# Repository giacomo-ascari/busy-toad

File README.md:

# busy-toad

## Intro

Stereophonic sound fx processor with line/instrument support, plus dedicated stereo headphone output.

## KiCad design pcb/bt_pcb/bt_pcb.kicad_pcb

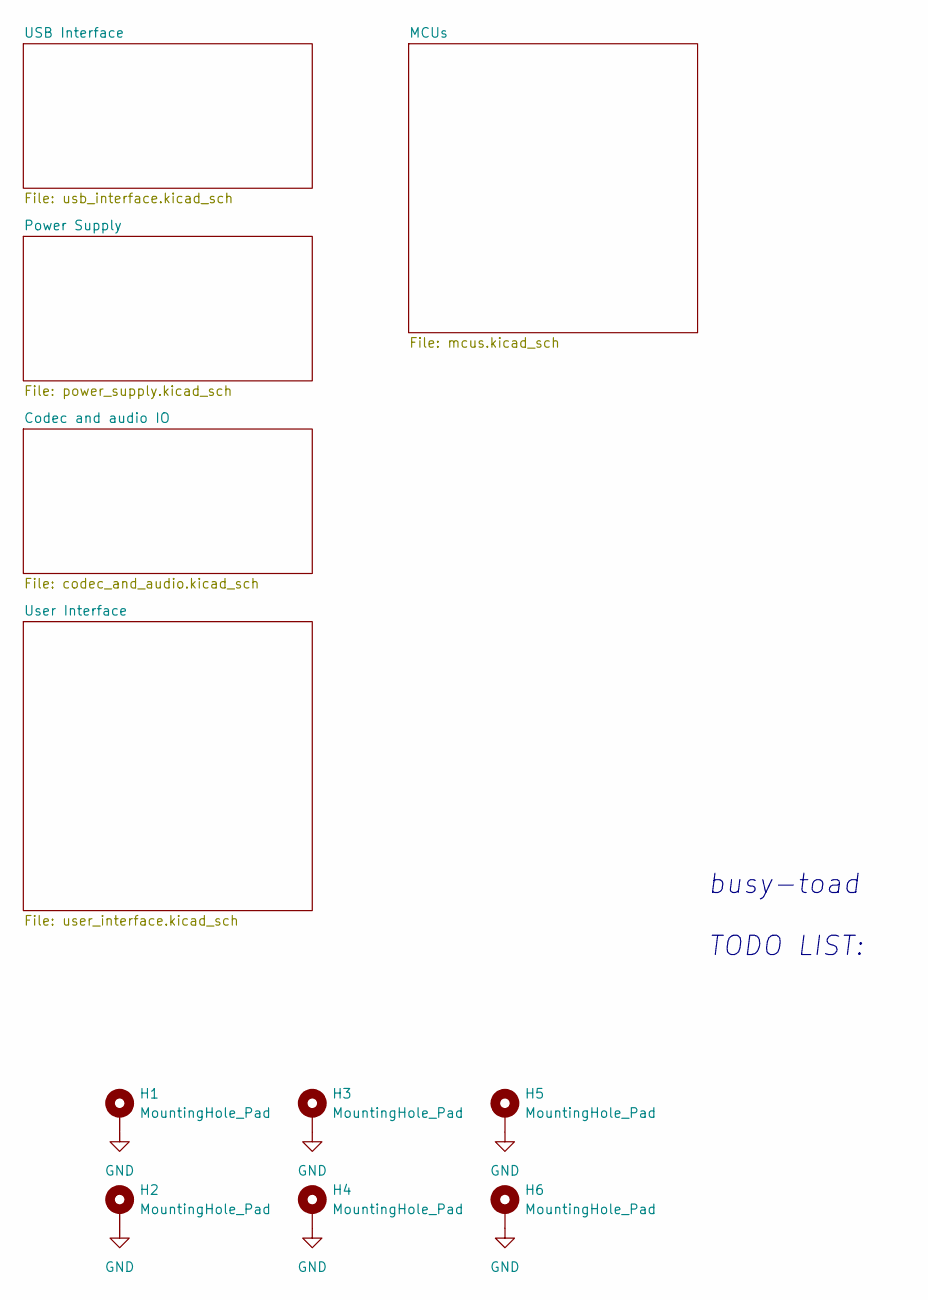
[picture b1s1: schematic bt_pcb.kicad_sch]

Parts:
H1, H2, H3, H4, H5, H6: MountingHole_Pad; MountingHole_3.2mm_M3_ISO14580_Pad

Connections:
GND: H1.1 (1_1), H2.1 (1_1), H3.1 (1_1), H4.1 (1_1), H5.1 (1_1), H6.1 (1_1); also elsewhere on the board

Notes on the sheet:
busy-toad TODO LIST:

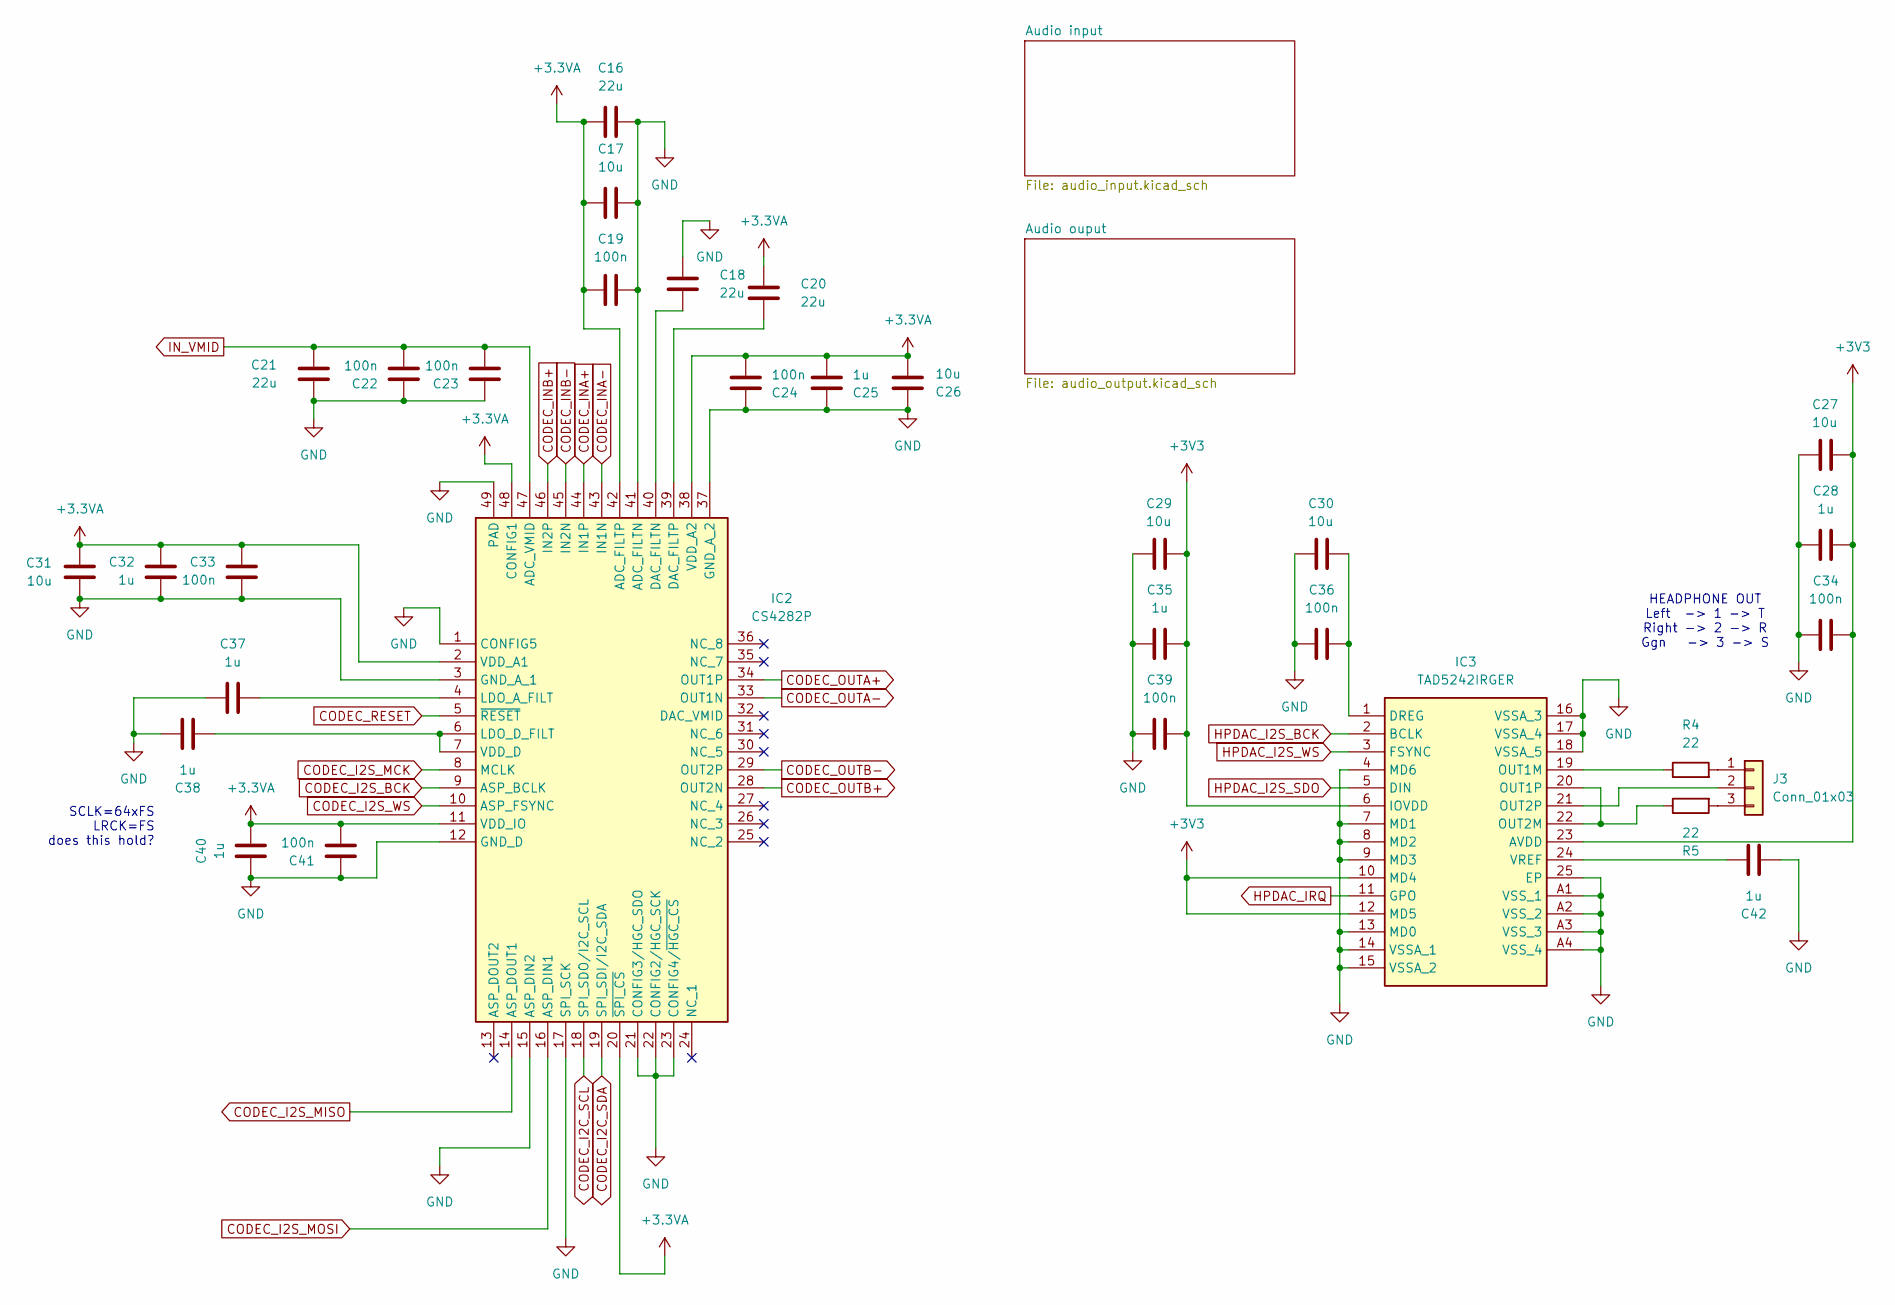
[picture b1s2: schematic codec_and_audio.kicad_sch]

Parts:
C16, C18, C20, C21: 22u; C_0805_2012Metric_Pad1.18x1.45mm_HandSolder
C17, C26, C27, C29, C30, C31: 10u; C_0805_2012Metric_Pad1.18x1.45mm_HandSolder
C19, C22, C23, C24, C33, C34, C36, C39, C41: 100n; C_0603_1608Metric_Pad1.08x0.95mm_HandSolder
C25, C28, C32, C35, C37, C38, C40, C42: 1u; C_0603_1608Metric_Pad1.08x0.95mm_HandSolder
IC2: CS4282P; QFN40P600X600X80-49N-D; Manufacturer_Part_Number CS4282P
IC3: TAD5242IRGER; Manufacturer_Part_Number TAD5242IRGER; Mouser Part Number 595-TAD5242IRGER
J3: Conn_01x03; JST_PH_B3B-PH-K_1x03_P2.00mm_Vertical
R4, R5: 22; R_0603_1608Metric_Pad0.98x0.95mm_HandSolder

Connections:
+3.3VA: C16.1, C17.2, C19.2, C20.1, C24.2, C25.2, C26.2, C31.1, C32.1, C33.1, C40.1, C41.2, IC2.2 (VDD_A1), IC2.11 (VDD_IO), IC2.20 (~SPI_CS), IC2.38 (VDD_A2), IC2.42 (ADC_FILTP), IC2.48 (CONFIG1); also elsewhere on the board
+3V3: C27.1, C28.1, C29.1, C34.2, C35.1, C39.2, IC3.6 (IOVDD), IC3.10 (MD4), IC3.12 (MD5), IC3.23 (AVDD); also elsewhere on the board
CODEC_I2C_SCL: IC2.18 (SPI_SDO/I2C_SCL); also elsewhere on the board
CODEC_I2C_SDA: IC2.19 (SPI_SDI/I2C_SDA); also elsewhere on the board
CODEC_I2S_BCK: IC2.9 (ASP_BCLK); also elsewhere on the board
CODEC_I2S_MCK: IC2.8 (MCLK); also elsewhere on the board
CODEC_I2S_MISO: IC2.14 (ASP_DOUT1); also elsewhere on the board
CODEC_I2S_MOSI: IC2.16 (ASP_DIN1); also elsewhere on the board
CODEC_I2S_WS: IC2.10 (ASP_FSYNC); also elsewhere on the board
CODEC_INA+: IC2.44 (IN1P); also elsewhere on the board
CODEC_INA-: IC2.43 (IN1N); also elsewhere on the board
CODEC_INB+: IC2.46 (IN2P); also elsewhere on the board
CODEC_INB-: IC2.45 (IN2N); also elsewhere on the board
CODEC_OUTA+: IC2.34 (OUT1P); also elsewhere on the board
CODEC_OUTA-: IC2.33 (OUT1N); also elsewhere on the board
CODEC_OUTB+: IC2.28 (OUT2N); also elsewhere on the board
CODEC_OUTB-: IC2.29 (OUT2P); also elsewhere on the board
CODEC_RESET: IC2.5 (~RESET); also elsewhere on the board
GND: C16.2, C17.1, C18.1, C19.1, C21.2, C22.1, C23.1, C24.1, C25.1, C26.1, C27.2, C28.2, C29.2, C30.2, C31.2, C32.2, C33.2, C34.1, C35.2, C36.1, C37.2, C38.2, C39.1, C40.2, C41.1, C42.2, IC2.1 (CONFIG5), IC2.3 (GND_A_1), IC2.12 (GND_D), IC2.15 (ASP_DIN2), IC2.17 (SPI_SCK), IC2.21 (CONFIG3/HGC_SDO), IC2.22 (CONFIG2/HGC_SCK), IC2.23 (CONFIG4/~HGC_CS), IC2.37 (GND_A_2), IC2.41 (ADC_FILTN), IC2.49 (PAD), IC3.4 (MD6), IC3.7 (MD1), IC3.8 (MD2), IC3.9 (MD3), IC3.13 (MD0), IC3.14 (VSSA_1), IC3.15 (VSSA_2), IC3.16 (VSSA_3), IC3.17 (VSSA_4), IC3.18 (VSSA_5), IC3.25 (EP), IC3.A1 (VSS_1), IC3.A2 (VSS_2), IC3.A3 (VSS_3), IC3.A4 (VSS_4); also elsewhere on the board
HPDAC_I2S_BCK: IC3.2 (BCLK); also elsewhere on the board
HPDAC_I2S_SDO: IC3.5 (DIN); also elsewhere on the board
HPDAC_I2S_WS: IC3.3 (FSYNC); also elsewhere on the board
HPDAC_IRQ: IC3.11 (GPO); also elsewhere on the board
IN_VMID: C21.1, C22.2, C23.2, IC2.47 (ADC_VMID); also elsewhere on the board
unnamed: C18.2, IC2.40 (DAC_FILTN)
unnamed: C20.2, IC2.39 (DAC_FILTP)
unnamed: C37.1, IC2.4 (LDO_A_FILT)
unnamed: C38.1, IC2.6 (LDO_D_FILT), IC2.7 (VDD_D)
unnamed: C30.1, C36.2, IC3.1 (DREG)
unnamed: IC3.19 (OUT1M), R4.1
unnamed: IC3.20 (OUT1P), IC3.22 (OUT2M), R5.1
unnamed: IC3.21 (OUT2P), J3.2
unnamed: C42.1, IC3.24 (VREF)
unnamed: J3.1, R4.2
unnamed: J3.3, R5.2

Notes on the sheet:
HEADPHONE OUT Left -> 1 -> T Right -> 2 -> R Ggn -> 3 -> S
SCLK=64xFS LRCK=FS does this hold?

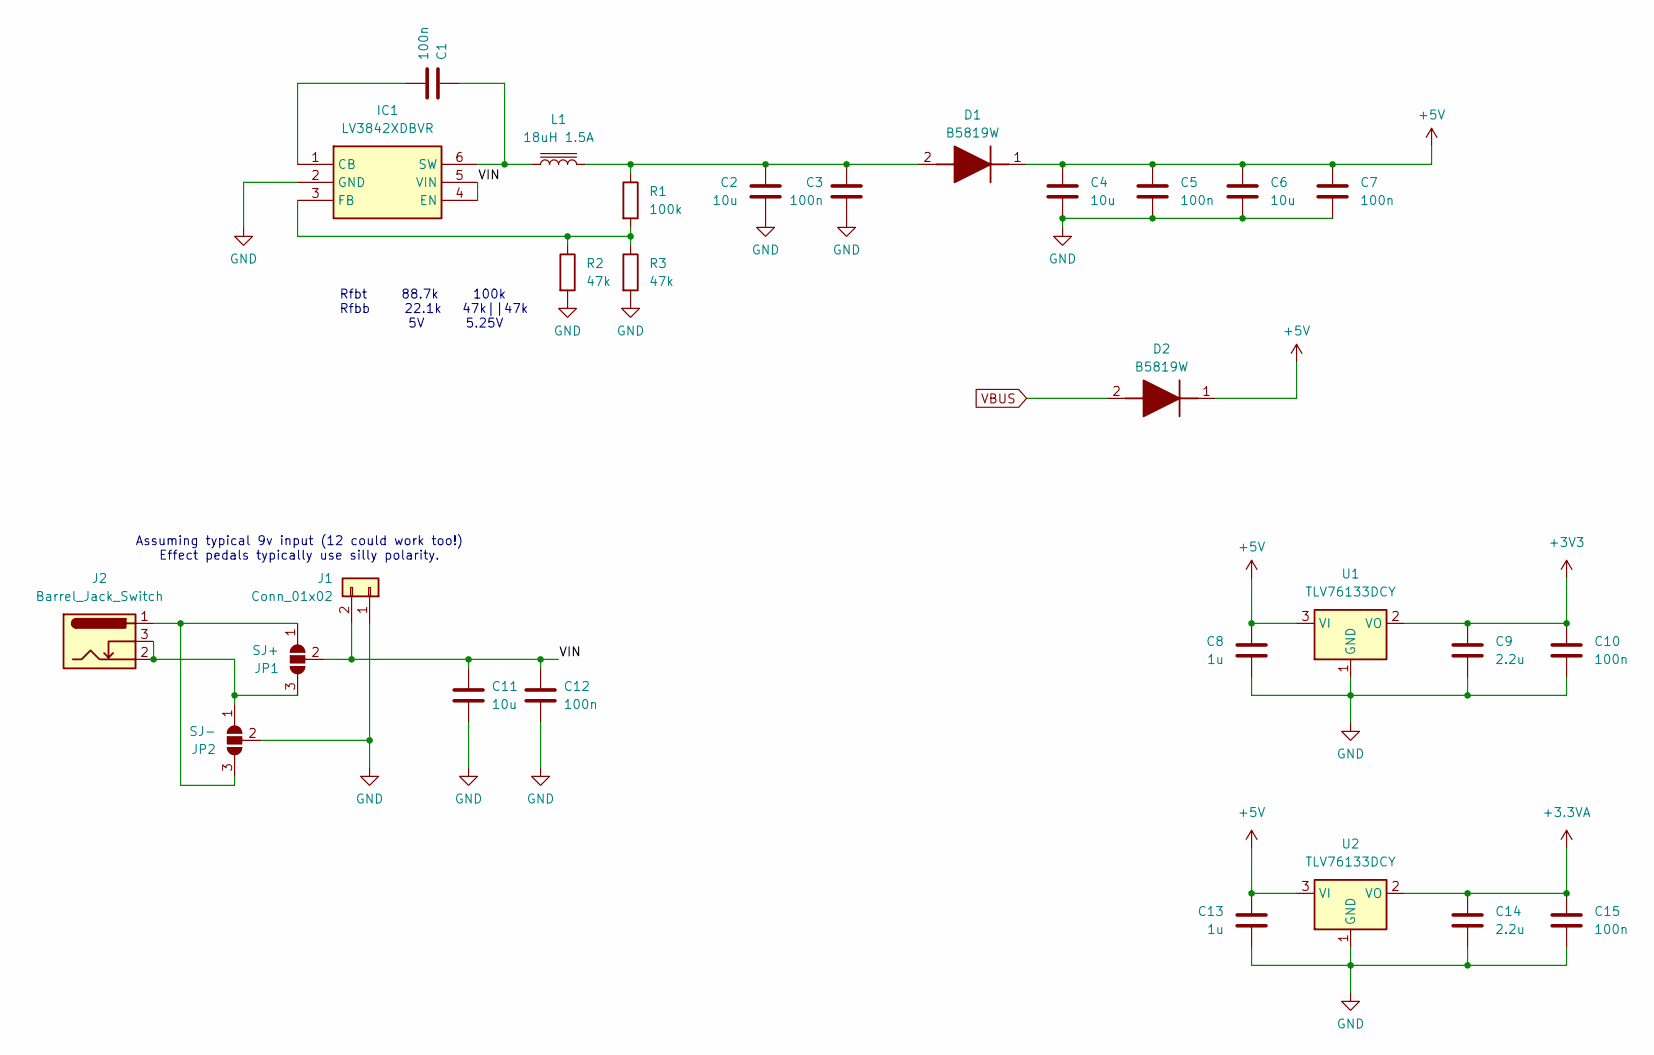
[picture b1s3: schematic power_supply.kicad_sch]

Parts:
C1, C3, C5, C7, C10, C12, C15: 100n; C_0603_1608Metric_Pad1.08x0.95mm_HandSolder
C2, C4, C6, C11: 10u; C_0805_2012Metric_Pad1.18x1.45mm_HandSolder
C8, C13: 1u; C_0603_1608Metric_Pad1.08x0.95mm_HandSolder
C9, C14: 2.2u; C_0603_1608Metric_Pad1.08x0.95mm_HandSolder
D1, D2: B5819W; SOD3716X125N; Manufacturer_Part_Number B5819W
IC1: LV3842XDBVR; SOT95P280X145-6N; Manufacturer_Part_Number LV3842XDBVR; Mouser Part Number 595-LV3842XDBVR
J1: Conn_01x02; PinHeader_1x02_P2.54mm_Vertical
J2: Barrel_Jack_Switch; 694106301002_1
JP1: SJ+; SolderJumper-3_P1.3mm_Open_Pad1.0x1.5mm
JP2: SJ-; SolderJumper-3_P1.3mm_Open_Pad1.0x1.5mm
L1: 18uH 1.5A; SRR6040A180M
R1: 100k; R_0603_1608Metric_Pad0.98x0.95mm_HandSolder
R2, R3: 47k; R_0603_1608Metric_Pad0.98x0.95mm_HandSolder
U1, U2: TLV76133DCY; SOT-223-3_TabPin2

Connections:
+3.3VA: C14.2, C15.1, U2.2 (VO); also elsewhere on the board
+3V3: C9.2, C10.1, U1.2 (VO); also elsewhere on the board
+5V: C4.1, C5.1, C6.1, C7.1, C8.2, C13.2, D1.1 (K), D2.1 (K), U1.3 (VI), U2.3 (VI)
/Power Supply/VIN: C11.1, C12.1, IC1.4 (EN), IC1.5 (VIN), J1.2, JP1.2 (C)
GND: C2.2, C3.2, C4.2, C5.2, C6.2, C7.2, C8.1, C9.1, C10.2, C11.2, C12.2, C13.1, C14.1, C15.2, IC1.2 (GND), J1.1, JP2.2 (C), R2.2, R3.2, U1.1 (GND), U2.1 (GND); also elsewhere on the board
unnamed: C2.1, C3.1, D1.2 (A), L1.2, R1.1
unnamed: C1.2, IC1.1 (CB)
unnamed: IC1.3 (FB), R1.2, R2.1, R3.1
unnamed: C1.1, IC1.6 (SW), L1.1
unnamed: J2.1, JP1.1 (A), JP2.3 (B)
unnamed: J2.2, J2.3, JP1.3 (B), JP2.1 (A)
VBUS: D2.2 (A); also elsewhere on the board

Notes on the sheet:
Assuming typical 9v input (12 could work too!) Effect pedals typically use silly polarity.
Rfbt 88.7k 100k Rfbb 22.1k 47k||47k 5V 5.25V

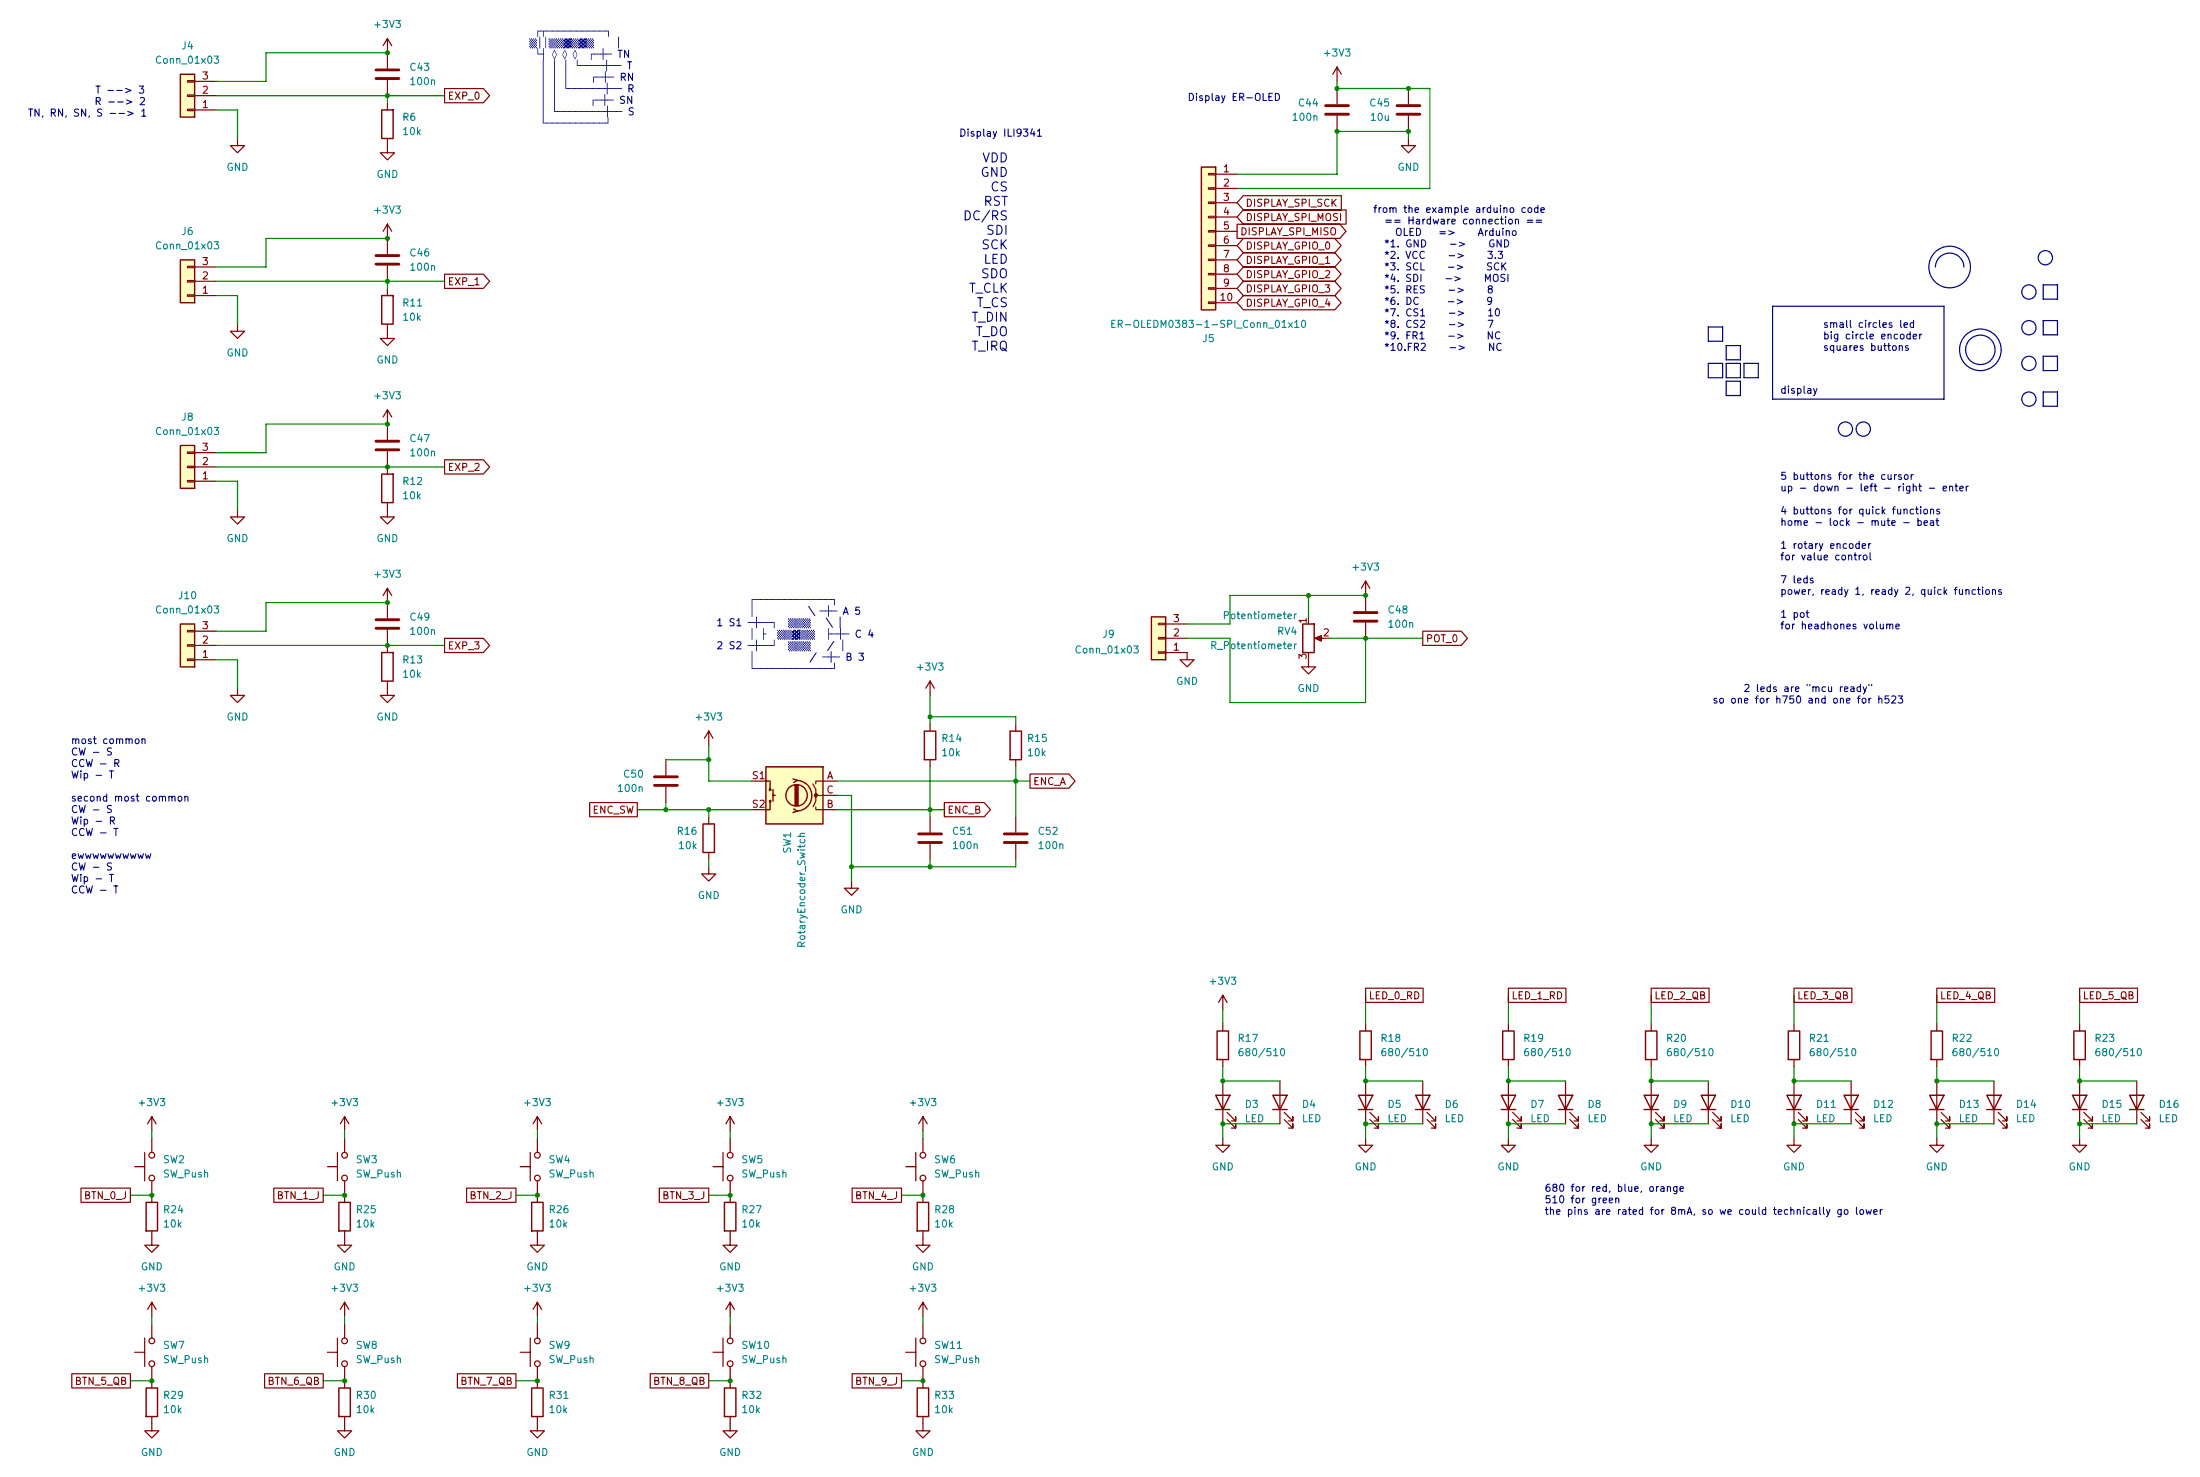
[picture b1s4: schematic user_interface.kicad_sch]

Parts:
C43, C44, C46, C47, C48, C49, C50, C51, C52: 100n; C_0603_1608Metric_Pad1.08x0.95mm_HandSolder
C45: 10u; C_0805_2012Metric_Pad1.18x1.45mm_HandSolder
D3, D5, D7, D9, D11, D13, D15: LED; LED_0603_1608Metric_Pad1.05x0.95mm_HandSolder
D4, D6, D8, D10, D12, D14, D16: LED; LED_D3.0mm
J4, J6, J8, J9, J10: Conn_01x03; JST_PH_B3B-PH-K_1x03_P2.00mm_Vertical
J5: ER-OLEDM0383-1-SPI_Conn_01x10; ER-OLEDM0383-1-SPI
R6, R11, R12, R13, R14, R15, R16, R24, R25, R26, R27, R28, R29, R30, R31, R32, R33: 10k; R_0603_1608Metric_Pad0.98x0.95mm_HandSolder
R17, R18, R19, R20, R21, R22, R23: 680/510; R_0603_1608Metric_Pad0.98x0.95mm_HandSolder
RV4: R_Potentiometer; Potentiometer_Alpha_RD901F-40-00D_Single_Vertical_CircularH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
SW1: RotaryEncoder_Switch; RotaryEncoder_Alps_EC11E-Switch_Vertical_H20mm_CircularMoun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
SW2, SW3, SW4, SW5, SW6, SW7, SW8, SW9, SW10, SW11: SW_Push; SW_TH_Tactile_Omron_B3F-102x

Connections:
+3V3: C43.1, C44.2, C45.2, C46.1, C47.1, C48.1, C49.1, C50.1, J4.3, J5.2, J6.3, J8.3, J9.3, J10.3, R14.1, R15.1, R17.1, RV4.1, SW1.S1, SW2.2, SW3.2, SW4.2, SW5.2, SW6.2, SW7.2, SW8.2, SW9.2, SW10.2, SW11.2; also elsewhere on the board
BTN_0_J: R24.1, SW2.1; also elsewhere on the board
BTN_1_J: R25.1, SW3.1; also elsewhere on the board
BTN_2_J: R26.1, SW4.1; also elsewhere on the board
BTN_3_J: R27.1, SW5.1; also elsewhere on the board
BTN_4_J: R28.1, SW6.1; also elsewhere on the board
BTN_5_QB: R29.1, SW7.1; also elsewhere on the board
BTN_6_QB: R30.1, SW8.1; also elsewhere on the board
BTN_7_QB: R31.1, SW9.1; also elsewhere on the board
BTN_8_QB: R32.1, SW10.1; also elsewhere on the board
BTN_9_J: R33.1, SW11.1; also elsewhere on the board
DISPLAY_GPIO_0: J5.6; also elsewhere on the board
DISPLAY_GPIO_1: J5.7; also elsewhere on the board
DISPLAY_GPIO_2: J5.8; also elsewhere on the board
DISPLAY_GPIO_3: J5.9; also elsewhere on the board
DISPLAY_GPIO_4: J5.10; also elsewhere on the board
DISPLAY_SPI_MISO: J5.5; also elsewhere on the board
DISPLAY_SPI_MOSI: J5.4; also elsewhere on the board
DISPLAY_SPI_SCK: J5.3; also elsewhere on the board
ENC_A: C52.1, R15.2, SW1.A; also elsewhere on the board
ENC_B: C51.1, R14.2, SW1.B; also elsewhere on the board
ENC_SW: C50.2, R16.1, SW1.S2; also elsewhere on the board
EXP_0: C43.2, J4.2, R6.2; also elsewhere on the board
EXP_1: C46.2, J6.2, R11.2; also elsewhere on the board
EXP_2: C47.2, J8.2, R12.2; also elsewhere on the board
EXP_3: C49.2, J10.2, R13.2; also elsewhere on the board
GND: C44.1, C45.1, C51.2, C52.2, D3.1 (K), D4.1 (K), D5.1 (K), D6.1 (K), D7.1 (K), D8.1 (K), D9.1 (K), D10.1 (K), D11.1 (K), D12.1 (K), D13.1 (K), D14.1 (K), D15.1 (K), D16.1 (K), J4.1, J5.1, J6.1, J8.1, J9.1, J10.1, R6.1, R11.1, R12.1, R13.1, R16.2, R24.2, R25.2, R26.2, R27.2, R28.2, R29.2, R30.2, R31.2, R32.2, R33.2, RV4.3, SW1.C; also elsewhere on the board
LED_0_RD: R18.1; also elsewhere on the board
LED_1_RD: R19.1; also elsewhere on the board
LED_2_QB: R20.1; also elsewhere on the board
LED_3_QB: R21.1; also elsewhere on the board
LED_4_QB: R22.1; also elsewhere on the board
LED_5_QB: R23.1; also elsewhere on the board
unnamed: D3.2 (A), D4.2 (A), R17.2
unnamed: D5.2 (A), D6.2 (A), R18.2
unnamed: D7.2 (A), D8.2 (A), R19.2
unnamed: D9.2 (A), D10.2 (A), R20.2
unnamed: D11.2 (A), D12.2 (A), R21.2
unnamed: D13.2 (A), D14.2 (A), R22.2
unnamed: D15.2 (A), D16.2 (A), R23.2
POT_0: C48.2, J9.2, RV4.2; also elsewhere on the board

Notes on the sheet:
680 for red, blue, orange 510 for green the pins are rated for 8mA, so we could technically go lower
small circles led big circle encoder squares buttons
Display ER-OLED
Display ILI9341
from the example arduino code == Hardware connection == OLED => Arduino *1. GND -> GND *2. VCC -> 3.3 *3. SCL -> SCK *4. SDI -> MOSI *5. RES -> 8 *6. DC -> 9 *7. CS1 -> 10 *8. CS2 -> 7 *9. FR1 -> NC *10.FR2 -> NC
VDD GND CS RST DC/RS SDI SCK LED SDO T_CLK T_CS T_DIN T_DO T_IRQ
5 buttons for the cursor up - down - left - right - enter 4 buttons for quick functions home - lock - mute - beat 1 rotary encoder for value control 7 leds power, ready 1, ready 2, quick functions 1 pot for headhones volume
most common CW - S CCW - R Wip - T second most common CW - S Wip - R CCW - T ewwwwwwwwww CW - S Wip - T CCW - T
T --> 3 R --> 2 TN, RN, SN, S --> 1
display
┌─────────────┐ │ \ ─┼─ A 5 1 S1 ─┼──┐ ▒▒▒ \ │ │ ├ ▒▒▓▒▒ ├─┼─ C 4 2 S2 ─┼──┘ ▒▒▒ / │ │ / ─┼─ B 3 └─────────────┘
┌┬──────────┐ ▒││▒▒▓▒▓▒ │ └┤ ◊ ◊ ◊ ┌─┼─ TN │ │ │ └────┼── T │ │ │ ┌─┼─ RN │ │ └──────┼── R │ │ ┌─┼─ SN │ └────────┼── S └──────────┘
2 leds are "mcu ready" so one for h750 and one for h523

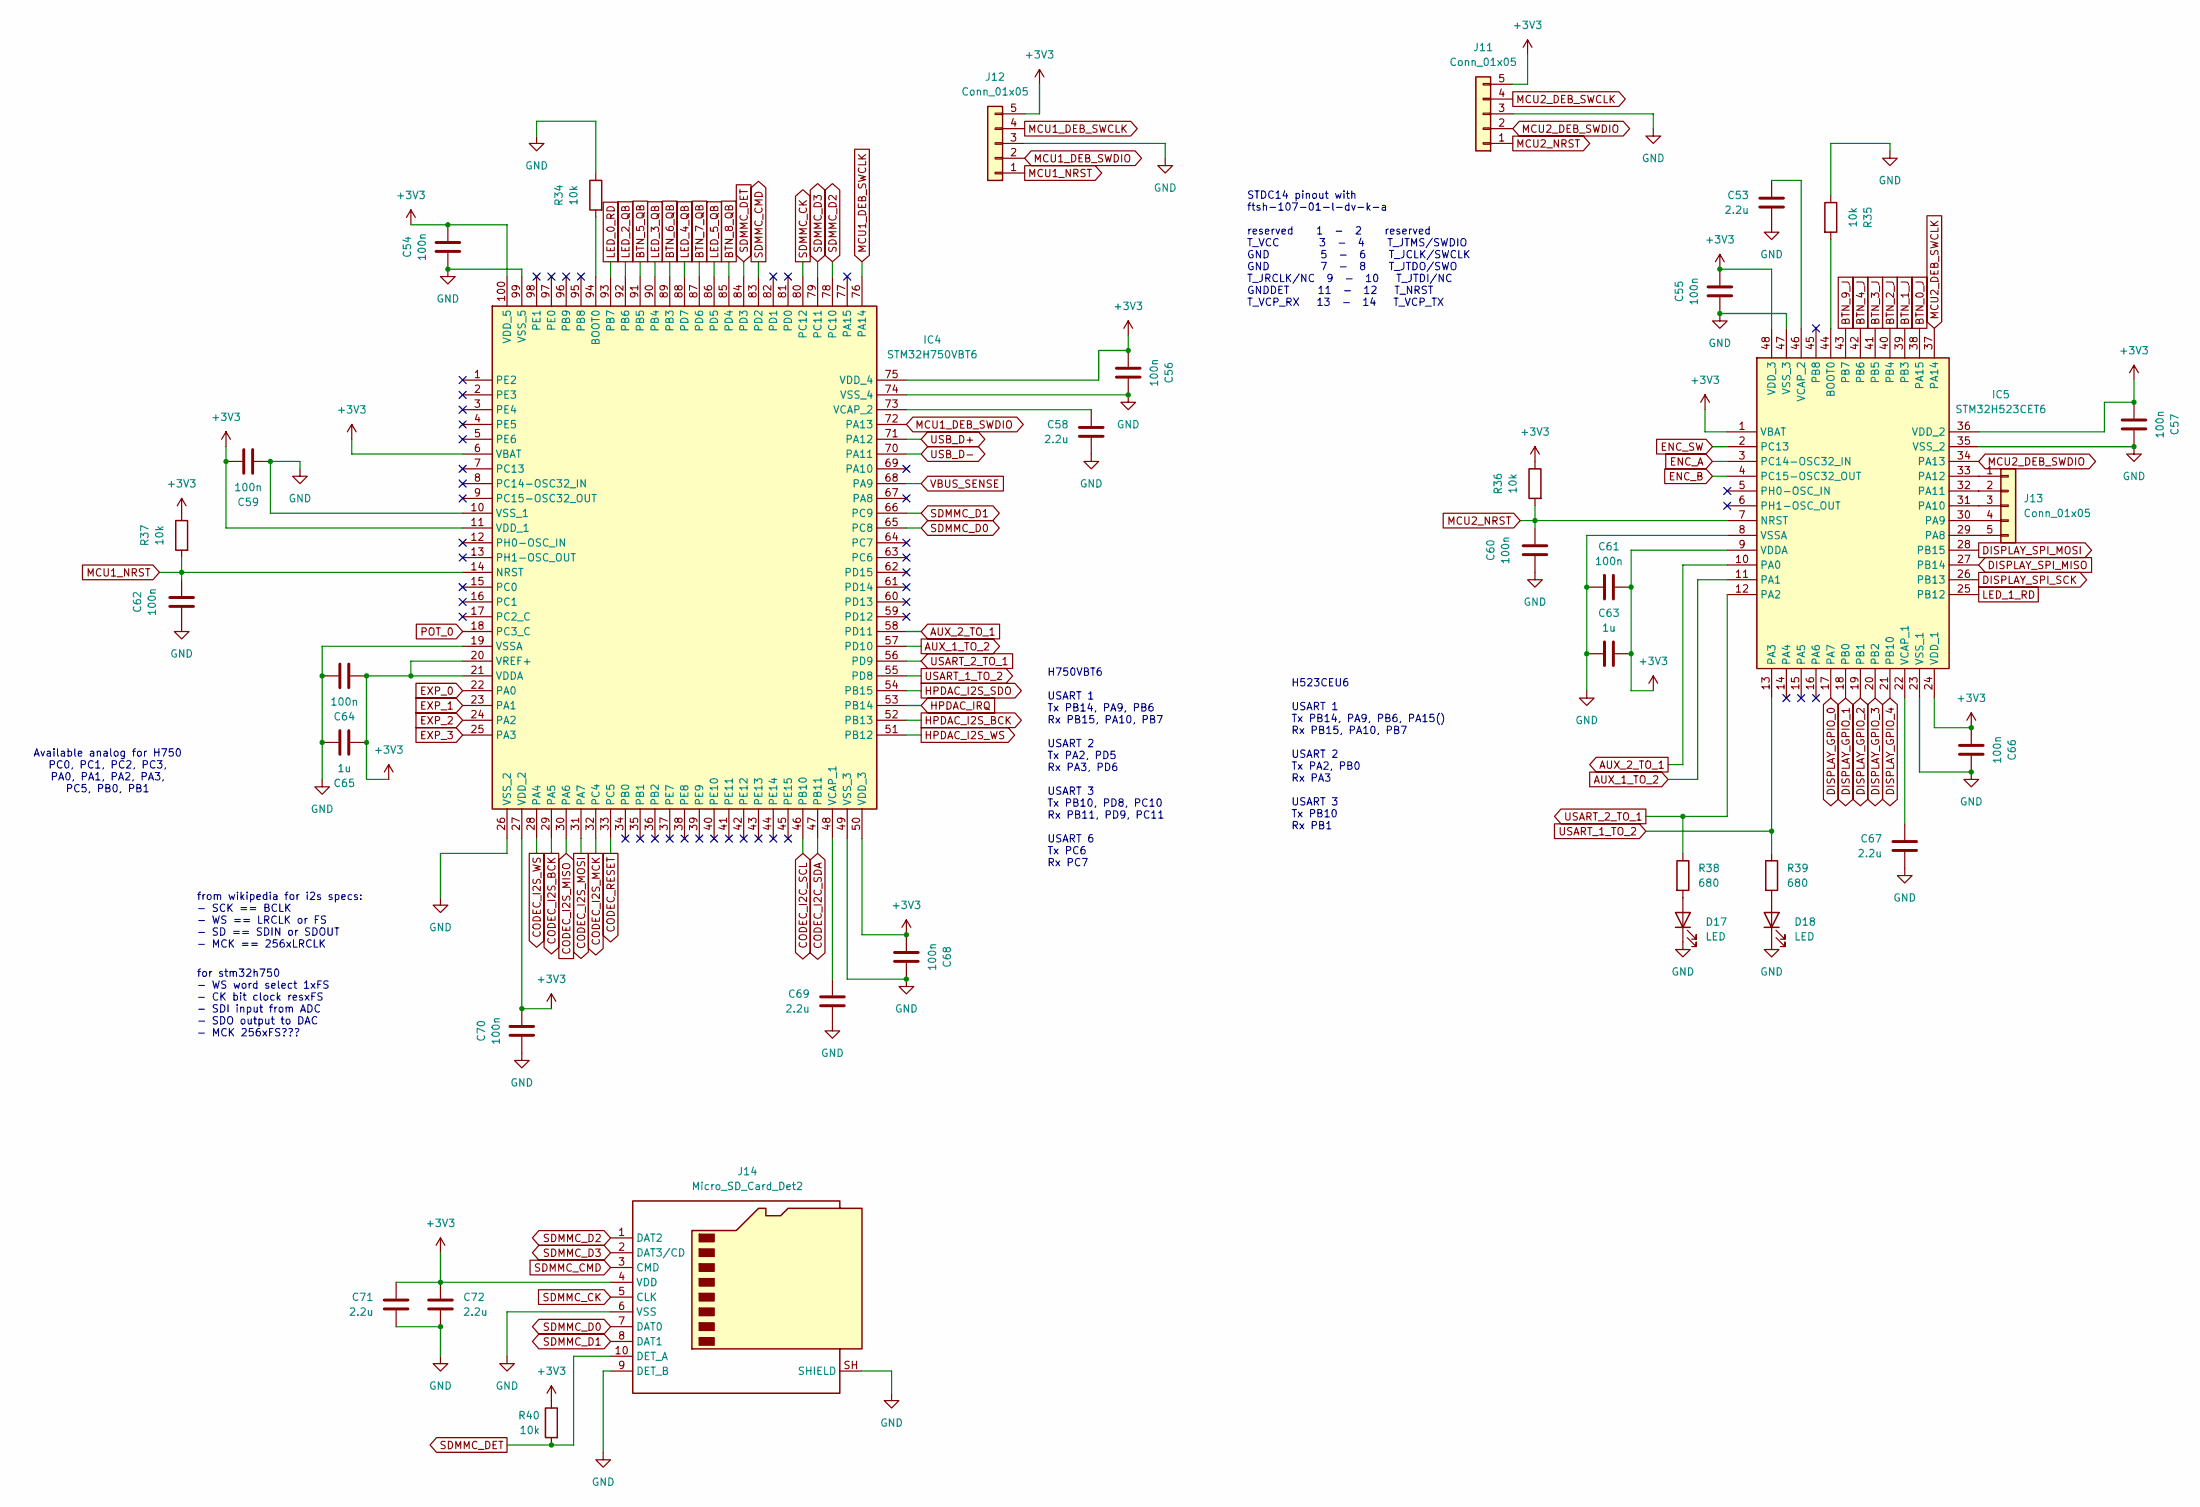
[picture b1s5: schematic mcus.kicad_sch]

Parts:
C53, C58, C67, C69, C71, C72: 2.2u; C_0603_1608Metric_Pad1.08x0.95mm_HandSolder
C54, C55, C56, C57, C59, C60, C61, C62, C64, C66, C68, C70: 100n; C_0603_1608Metric_Pad1.08x0.95mm_HandSolder
C63, C65: 1u; C_0603_1608Metric_Pad1.08x0.95mm_HandSolder
D17, D18: LED; LED_0603_1608Metric_Pad1.05x0.95mm_HandSolder
IC4: STM32H750VBT6; QFP50P1600X1600X160-100N; Manufacturer_Part_Number STM32H750VBT6; Mouser Part Number 511-STM32H750VBT6
IC5: STM32H523CET6; QFP50P900X900X160-48N; Manufacturer_Part_Number STM32H523CET6; Mouser Part Number 511-STM32H523CET6
J11, J12, J13: Conn_01x05; JST_PH_B5B-PH-K_1x05_P2.00mm_Vertical
J14: Micro_SD_Card_Det2; microSD_HC_Molex_104031-0811
R34, R35, R36, R37, R40: 10k; R_0603_1608Metric_Pad0.98x0.95mm_HandSolder
R38, R39: 680; R_0603_1608Metric_Pad0.98x0.95mm_HandSolder

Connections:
+3V3: C54.1, C55.1, C56.1, C57.1, C59.1, C61.1, C63.1, C64.1, C65.1, C66.1, C68.1, C70.2, C71.1, C72.1, IC4.6 (VBAT), IC4.11 (VDD_1), IC4.20 (VREF+), IC4.21 (VDDA), IC4.27 (VDD_2), IC4.50 (VDD_3), IC4.75 (VDD_4), IC4.100 (VDD_5), IC5.1 (VBAT), IC5.9 (VDDA), IC5.24 (VDD_1), IC5.36 (VDD_2), IC5.48 (VDD_3), J11.5, J12.5, J14.4 (VDD), R36.1, R37.1, R40.1; also elsewhere on the board
AUX_1_TO_2: IC4.57 (PD10), IC5.11 (PA1)
AUX_2_TO_1: IC4.58 (PD11), IC5.10 (PA0)
BTN_0_J: IC5.38 (PA15); also elsewhere on the board
BTN_1_J: IC5.39 (PB3); also elsewhere on the board
BTN_2_J: IC5.40 (PB4); also elsewhere on the board
BTN_3_J: IC5.41 (PB5); also elsewhere on the board
BTN_4_J: IC5.42 (PB6); also elsewhere on the board
BTN_5_QB: IC4.91 (PB5); also elsewhere on the board
BTN_6_QB: IC4.89 (PB3); also elsewhere on the board
BTN_7_QB: IC4.87 (PD6); also elsewhere on the board
BTN_8_QB: IC4.85 (PD4); also elsewhere on the board
BTN_9_J: IC5.43 (PB7); also elsewhere on the board
CODEC_I2C_SCL: IC4.46 (PB10); also elsewhere on the board
CODEC_I2C_SDA: IC4.47 (PB11); also elsewhere on the board
CODEC_I2S_BCK: IC4.29 (PA5); also elsewhere on the board
CODEC_I2S_MCK: IC4.32 (PC4); also elsewhere on the board
CODEC_I2S_MISO: IC4.30 (PA6); also elsewhere on the board
CODEC_I2S_MOSI: IC4.31 (PA7); also elsewhere on the board
CODEC_I2S_WS: IC4.28 (PA4); also elsewhere on the board
CODEC_RESET: IC4.33 (PC5); also elsewhere on the board
DISPLAY_GPIO_0: IC5.17 (PA7); also elsewhere on the board
DISPLAY_GPIO_1: IC5.18 (PB0); also elsewhere on the board
DISPLAY_GPIO_2: IC5.19 (PB1); also elsewhere on the board
DISPLAY_GPIO_3: IC5.20 (PB2); also elsewhere on the board
DISPLAY_GPIO_4: IC5.21 (PB10); also elsewhere on the board
DISPLAY_SPI_MISO: IC5.27 (PB14); also elsewhere on the board
DISPLAY_SPI_MOSI: IC5.28 (PB15); also elsewhere on the board
DISPLAY_SPI_SCK: IC5.26 (PB13); also elsewhere on the board
ENC_A: IC5.3 (PC14-OSC32_IN); also elsewhere on the board
ENC_B: IC5.4 (PC15-OSC32_OUT); also elsewhere on the board
ENC_SW: IC5.2 (PC13); also elsewhere on the board
EXP_0: IC4.22 (PA0); also elsewhere on the board
EXP_1: IC4.23 (PA1); also elsewhere on the board
EXP_2: IC4.24 (PA2); also elsewhere on the board
EXP_3: IC4.25 (PA3); also elsewhere on the board
GND: C53.2, C54.2, C55.2, C56.2, C57.2, C58.2, C59.2, C60.1, C61.2, C62.1, C63.2, C64.2, C65.2, C66.2, C67.2, C68.2, C69.2, C70.1, C71.2, C72.2, D17.1 (K), D18.1 (K), IC4.10 (VSS_1), IC4.19 (VSSA), IC4.26 (VSS_2), IC4.49 (VSS_3), IC4.74 (VSS_4), IC4.99 (VSS_5), IC5.8 (VSSA), IC5.23 (VSS_1), IC5.35 (VSS_2), IC5.47 (VSS_3), J11.3, J12.3, J14.6 (VSS), J14.9 (DET_B), J14.SH (SHIELD), R34.1, R35.1; also elsewhere on the board
HPDAC_I2S_BCK: IC4.52 (PB13); also elsewhere on the board
HPDAC_I2S_SDO: IC4.54 (PB15); also elsewhere on the board
HPDAC_I2S_WS: IC4.51 (PB12); also elsewhere on the board
HPDAC_IRQ: IC4.53 (PB14); also elsewhere on the board
LED_0_RD: IC4.93 (PB7); also elsewhere on the board
LED_1_RD: IC5.25 (PB12); also elsewhere on the board
LED_2_QB: IC4.92 (PB6); also elsewhere on the board
LED_3_QB: IC4.90 (PB4); also elsewhere on the board
LED_4_QB: IC4.88 (PD7); also elsewhere on the board
LED_5_QB: IC4.86 (PD5); also elsewhere on the board
MCU1_DEB_SWCLK: IC4.76 (PA14), J12.4
MCU1_DEB_SWDIO: IC4.72 (PA13), J12.2
MCU1_NRST: C62.2, IC4.14 (NRST), J12.1, R37.2
MCU2_DEB_SWCLK: IC5.37 (PA14), J11.4
MCU2_DEB_SWDIO: IC5.34 (PA13), J11.2
MCU2_NRST: C60.2, IC5.7 (NRST), J11.1, R36.2
unnamed: D17.2 (A), R38.2
unnamed: D18.2 (A), R39.2
unnamed: IC4.94 (BOOT0), R34.2
unnamed: C69.1, IC4.48 (VCAP_1)
unnamed: C58.1, IC4.73 (VCAP_2)
unnamed: IC5.44 (BOOT0), R35.2
unnamed: IC5.29 (PA8), J13.5
unnamed: IC5.30 (PA9), J13.4
unnamed: IC5.31 (PA10), J13.3
unnamed: IC5.32 (PA11), J13.2
unnamed: IC5.33 (PA12), J13.1
unnamed: C67.1, IC5.22 (VCAP_1)
unnamed: C53.1, IC5.46 (VCAP_2)
POT_0: IC4.18 (PC3_C); also elsewhere on the board
SDMMC_CK: IC4.80 (PC12), J14.5 (CLK)
SDMMC_CMD: IC4.83 (PD2), J14.3 (CMD)
SDMMC_D0: IC4.65 (PC8), J14.7 (DAT0)
SDMMC_D1: IC4.66 (PC9), J14.8 (DAT1)
SDMMC_D2: IC4.78 (PC10), J14.1 (DAT2)
SDMMC_D3: IC4.79 (PC11), J14.2 (DAT3/CD)
SDMMC_DET: IC4.84 (PD3), J14.10 (DET_A), R40.2
USART_1_TO_2: IC4.55 (PD8), IC5.13 (PA3), R39.1
USART_2_TO_1: IC4.56 (PD9), IC5.12 (PA2), R38.1
USB_D+: IC4.71 (PA12); also elsewhere on the board
USB_D-: IC4.70 (PA11); also elsewhere on the board
VBUS_SENSE: IC4.68 (PA9); also elsewhere on the board

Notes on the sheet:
H523CEU6 USART 1 Tx PB14, PA9, PB6, PA15() Rx PB15, PA10, PB7 USART 2 Tx PA2, PB0 Rx PA3 USART 3 Tx PB10 Rx PB1
for stm32h750 - WS word select 1xFS - CK bit clock resxFS - SDI input from ADC - SDO output to DAC - MCK 256xFS???
H750VBT6 USART 1 Tx PB14, PA9, PB6 Rx PB15, PA10, PB7 USART 2 Tx PA2, PD5 Rx PA3, PD6 USART 3 Tx PB10, PD8, PC10 Rx PB11, PD9, PC11 USART 6 Tx PC6 Rx PC7
STDC14 pinout with ftsh-107-01-l-dv-k-a reserved 1 - 2 reserved T_VCC 3 - 4 T_JTMS/SWDIO GND 5 - 6 T_JCLK/SWCLK GND 7 - 8 T_JTDO/SWO T_JRCLK/NC 9 - 10 T_JTDI/NC GNDDET 11 - 12 T_NRST T_VCP_RX 13 - 14 T_VCP_TX
from wikipedia for i2s specs: - SCK == BCLK - WS == LRCLK or FS - SD == SDIN or SDOUT - MCK == 256xLRCLK
Available analog for H750 PC0, PC1, PC2, PC3, PA0, PA1, PA2, PA3, PC5, PB0, PB1

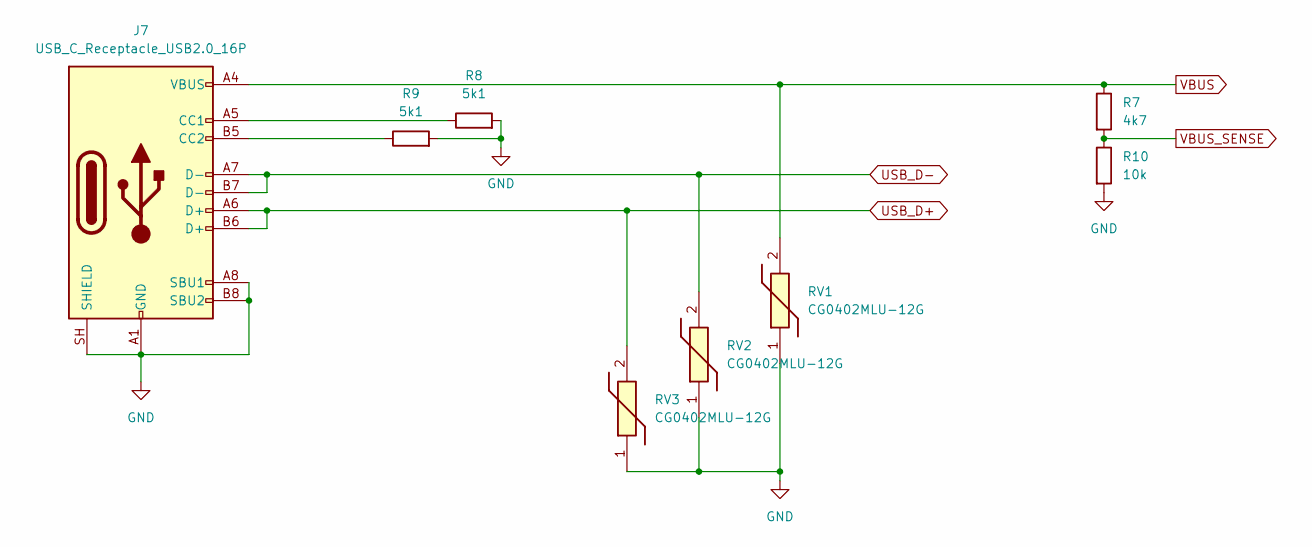
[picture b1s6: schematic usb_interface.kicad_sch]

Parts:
J7: USB_C_Receptacle_USB2.0_16P; USB_C_Receptacle_GCT_USB4105-xx-A_16P_TopMnt_Horizontal
R7: 4k7; R_0603_1608Metric_Pad0.98x0.95mm_HandSolder
R8, R9: 5k1; R_0603_1608Metric_Pad0.98x0.95mm_HandSolder
R10: 10k; R_0603_1608Metric_Pad0.98x0.95mm_HandSolder
RV1, RV2, RV3: CG0402MLU-12G; VARC1005X41N; Manufacturer_Part_Number CG0402MLU-12G; Mouser Part Number 652-CG0402MLU-12G

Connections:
GND: J7.A1 (GND), J7.A8 (SBU1), J7.A12 (GND), J7.B1 (GND), J7.B8 (SBU2), J7.B12 (GND), J7.SH (SHIELD), R8.2, R9.2, R10.2, RV1.1, RV2.1, RV3.1; also elsewhere on the board
unnamed: J7.A5 (CC1), R8.1
unnamed: J7.B5 (CC2), R9.1
USB_D+: J7.A6 (D+), J7.B6 (D+), RV3.2; also elsewhere on the board
USB_D-: J7.A7 (D-), J7.B7 (D-), RV2.2; also elsewhere on the board
VBUS: J7.A4 (VBUS), J7.A9 (VBUS), J7.B4 (VBUS), J7.B9 (VBUS), R7.1, RV1.2; also elsewhere on the board
VBUS_SENSE: R7.2, R10.1; also elsewhere on the board
